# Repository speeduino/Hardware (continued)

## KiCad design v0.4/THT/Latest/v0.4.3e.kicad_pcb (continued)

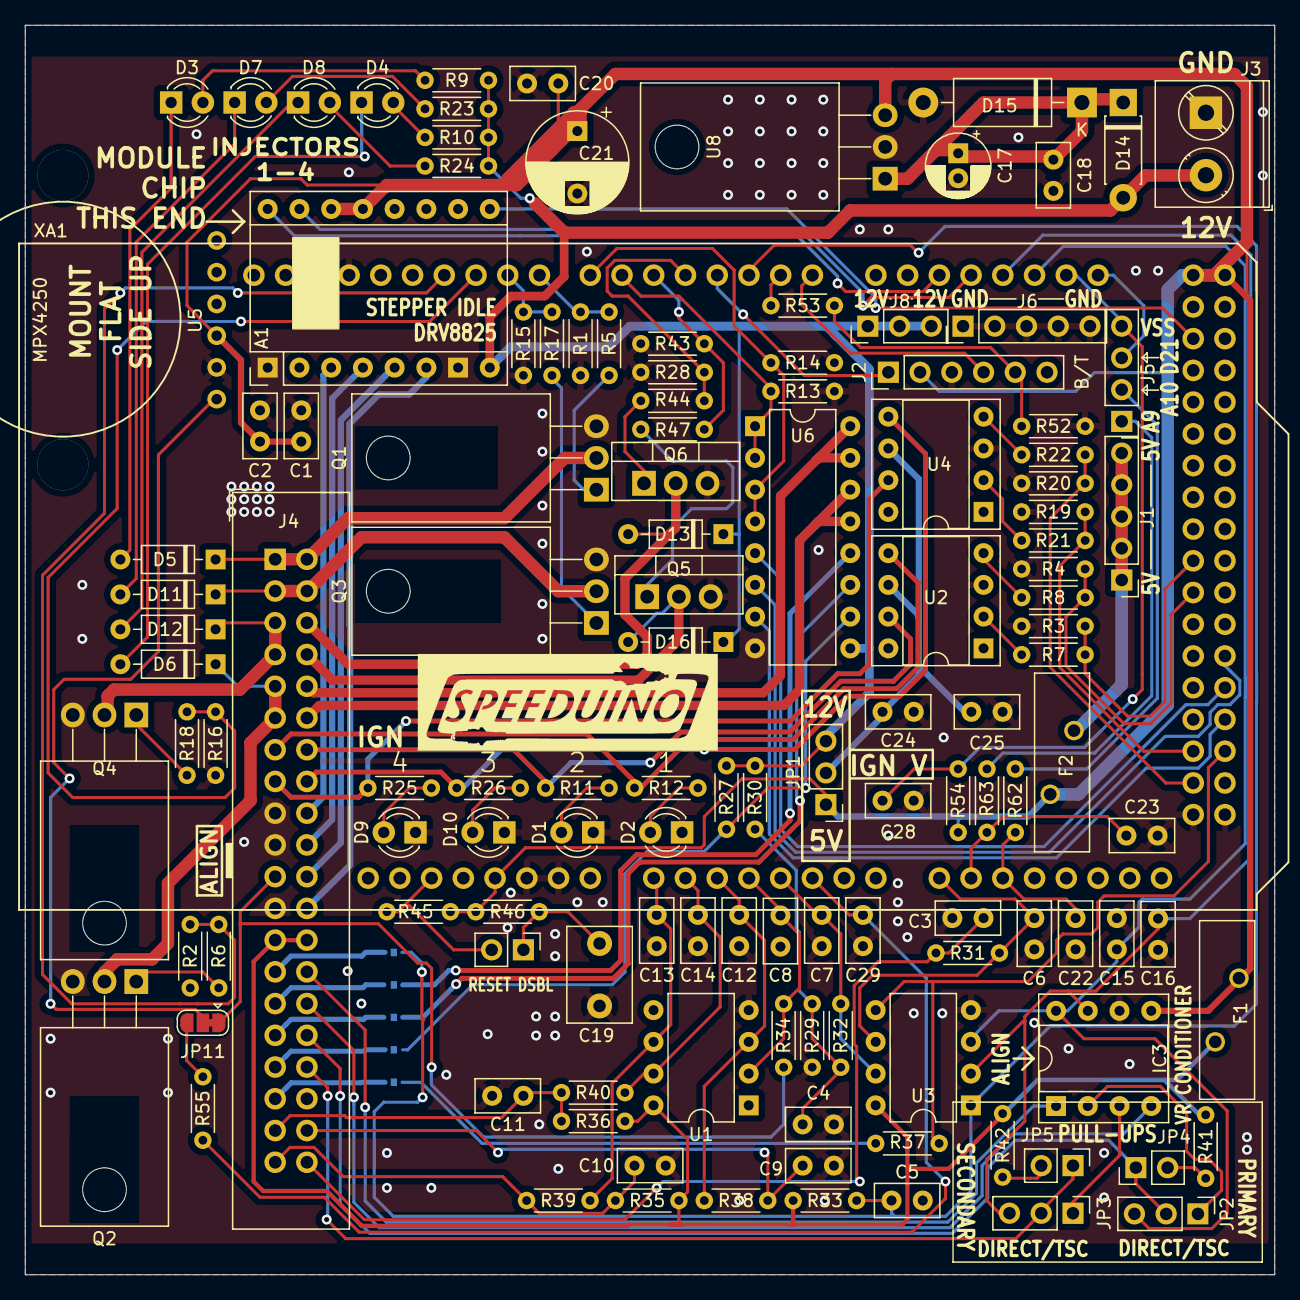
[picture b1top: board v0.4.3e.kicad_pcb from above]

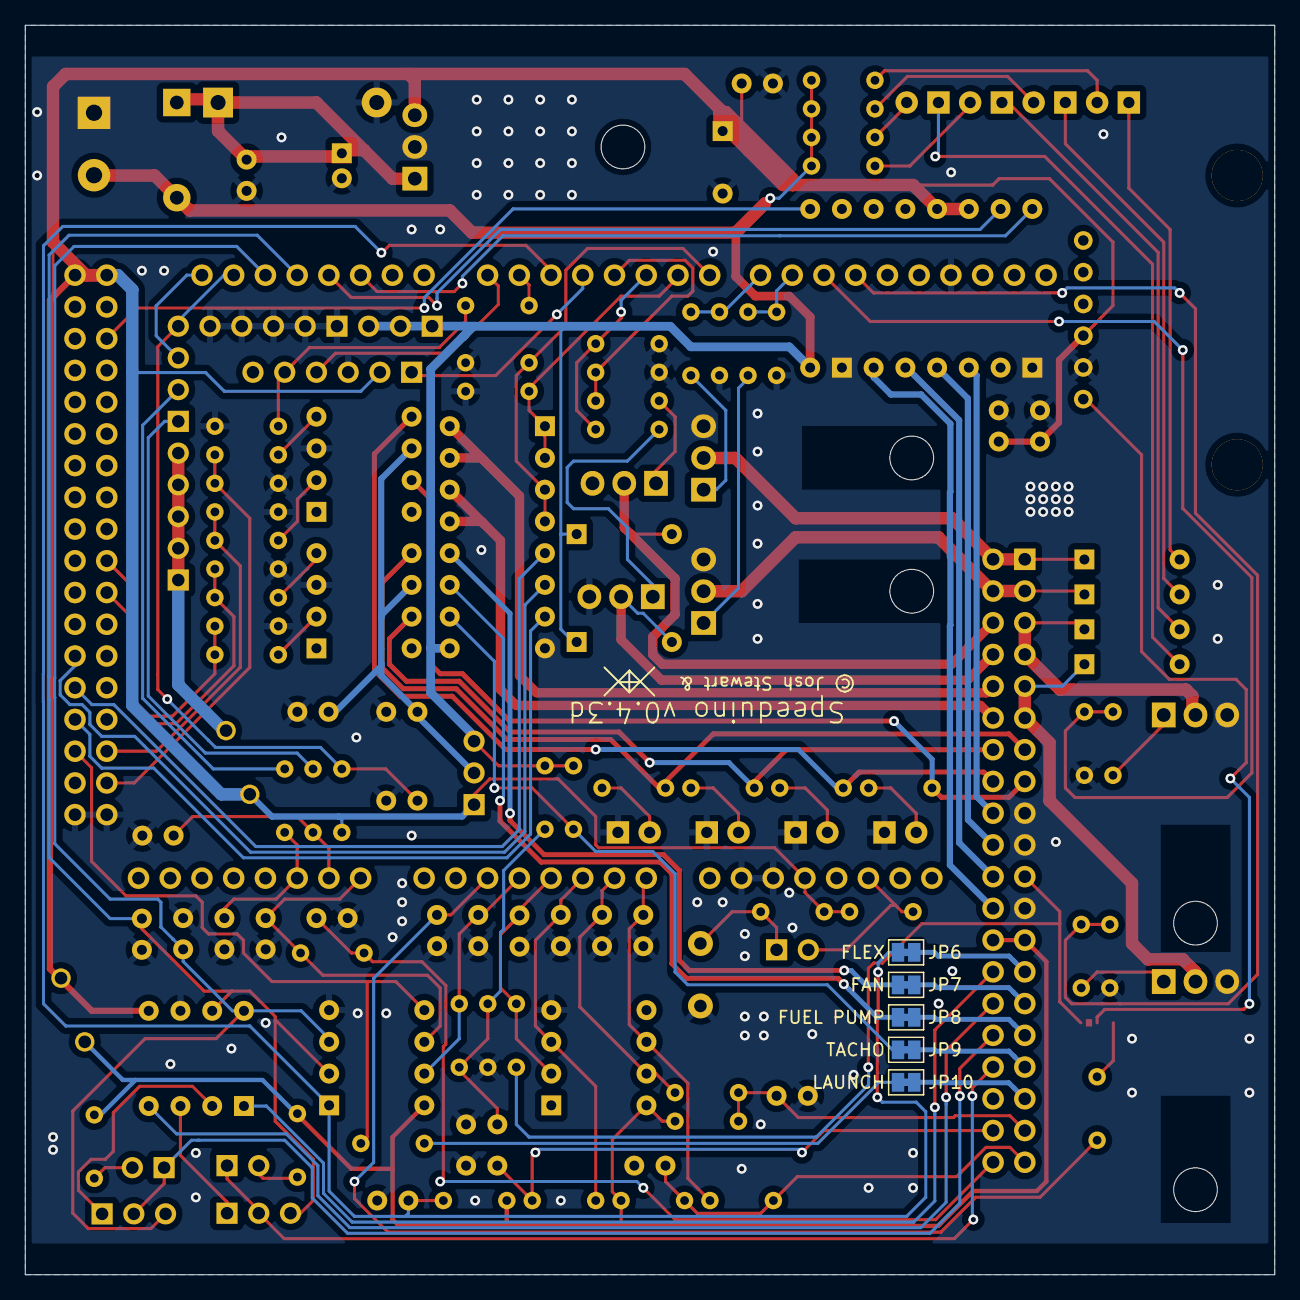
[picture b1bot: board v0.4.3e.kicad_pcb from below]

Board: 2 copper layers, 100.0 x 100.0 mm, 133 parts (5 on the bottom side), 111 nets.

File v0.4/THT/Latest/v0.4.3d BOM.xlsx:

| Speeduino BOM |  |  | v0.4.3d
Reference | Quantity | Value | Manufacturer_Name | Manufacturer_Part_Number | Footprint | URL | Digikey Part Number | Digikey BOM import
A1 | 2 | DRV8825 socket | Sullins | PPTC081LFBN-RC | Module:Pololu_Breakout-16_15.2x20.3mm | https://www.digikey.com.au/products/en?keywords=PPTC081LFBN-RC | S7006-ND | 2,S7006-ND
C1 C15 | 2 | 0.01uF | TDK | FA18X7R1H103KNU06 | Capacitor_THT:C_Disc_D5.0mm_W2.5mm_P2.50mm | https://www.digikey.com.au/product-detail/en/tdk-corporation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 | 445-174244-1-ND | 2,445-174244-1-ND
C17 | 1 | 10uF | Panasonic | EEU-FC1H100L | Capacitor_THT:CP_Radial_D5.0mm_P2.00mm | https://www.digikey.com.au/product-detail/en/panasonic-elect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 | P10316-ND | 1,P10316-ND
C19 | 1 | 22uF | TDK | FA22X7R1E226MRU06 | Capacitor_THT:C_Disc_D7.5mm_W5.0mm_P5.00mm |  | 445-180603-1-ND | 1,445-180603-1-ND
C21 | 1 | 47uF | Panasonic | EEU-FC1H470B | Capacitor_THT:CP_Radial_D8.0mm_P5.00mm |  | P19658CT-ND | 1,P19658CT-ND
C3 C4 C9 C10 C11 C16 C18 C20 C22 C23 C24 C28 | 12 | 0.1uF | TDK | FA18X8R1E104KNU06 | Capacitor_THT:C_Disc_D5.0mm_W2.5mm_P2.50mm | https://www.digikey.com.au/product-detail/en/tdk-corporation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 | 445-180563-1-ND | 12,445-180563-1-ND
C2 C25 | 2 | 1uF | TDK | FA18X7R1E105KRU06 | Capacitor_THT:C_Disc_D5.0mm_W2.5mm_P2.50mm | https://www.digikey.com.au/product-detail/en/tdk-corporation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 | 445-180543-1-ND | 2,445-180543-1-ND
C5 C6 C7 C12 C13 C14 | 6 | 0.22uF | TDK | FA18X8R1E224KRU06 | Capacitor_THT:C_Disc_D5.0mm_W2.5mm_P2.50mm | https://www.digikey.com.au/product-detail/en/tdk-corporation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 | 445-180564-1-ND | 6,445-180564-1-ND
C8 C29 | 2 | 470pf | TDK | FA18NP01H471JNU06 | Capacitor_THT:C_Disc_D5.0mm_W2.5mm_P2.50mm | https://www.digikey.com.au/product-detail/en/tdk-corporation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 | 445-180522-1-ND | 2,445-180522-1-ND
D5 D6 D11 D12 D13 D16 | 6 | Diode - General purpose | Vishay | 1N914TAP | Diode_THT:D_DO-35_SOD27_P7.62mm_Horizontal | https://www.digikey.com.au/product-detail/en/vishay-general-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 | 1N914TAPGICT-ND | 6,1N914TAPGICT-ND
D14 | 1 | SB230TA | SMC | SB230TA | Diode_THT:D_DO-41_SOD81_P7.62mm_Horizontal | https://www.digikey.com.au/product-detail/en/smc-diode-solut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 | 1655-1518-1-ND | 1,1655-1518-1-ND
D15 | 1 | D_TVS | Littelfuse | TP6KE47A | Diode_THT:D_DO-15_P12.70mm_Horizontal |  | F6853CT-ND | 1,F6853CT-ND
D1 D2 D3 D4 D7 D8 D9 D10 | 8 | LED | Wurth | 151031SS04000 | LED_THT:LED_D3.0mm | https://www.digikey.com.au/product-detail/en/w%C3%BCrth-elek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 | 732-5005-ND | 8,732-5005-ND
F1 F2 | 2 | Polyfuse | Bel Fuse | 0ZRP0050FF1E | Fuse:Fuse_BelFuse_0ZRE0055FF_L14.0mm_W4.1mm | https://www.digikey.com.au/product-detail/en/bel-fuse-inc/0Z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 | 507-2403-ND | 2,507-2403-ND
IC3 | 2 | Trig Cond Socket | Sullins Connector Solutions | PPTC041LFBN-RC | Package_DIP:DIP-8_W7.62mm_Socket |  | S7002-ND | 2,S7002-ND
J4 | 1 | Conn_02x20_Counter_Clockwise | Sullins | SBH11-PBPC-D20-ST-BK | Connector_IDC:IDC-Header_2x20_P2.54mm_Vertical | https://www.digikey.com.au/product-detail/en/sullins-connect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 | S9175-ND | 1,S9175-ND
Q1 Q2 Q3 Q4 | 4 | N-Channel MOSFET | ST | STP62NS04Z | Package_TO_SOT_THT:TO-220-3_Horizontal_TabDown |  | 497-5896-5-ND | 4,497-5896-5-ND
Q5 Q6 | 2 | Q_NMOS_GDSD | Vishay | IRLD024PBF | Package_DIP:Vishay_HVM-DIP-3_W7.62mm | https://www.digikey.com.au/product-detail/en/vishay-siliconi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 | IRLD024PBF-ND | 2,IRLD024PBF-ND
R1 R2 R3 R4 R13 R14 R15 R16 R19 R20 R28 R43 | 12 | 100k | Vishay | MBA02040C1003FCT00 | Resistor_THT:R_Axial_DIN0204_L3.6mm_D1.6mm_P5.08mm_Horizontal | https://www.digikey.com.au/product-detail/en/vishay-beyschla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 | BC3240CT-ND | 12,BC3240CT-ND
R9 R10 R11 R12 R23 R24 R25 R26 R33 | 9 | 2.4k | Vishay | MBA02040C2401FC100 | Resistor_THT:R_Axial_DIN0204_L3.6mm_D1.6mm_P5.08mm_Horizontal | https://www.digikey.com.au/product-detail/en/vishay-beyschla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 | BC3483CT-ND | 9,BC3483CT-ND
R30 | 1 | 3.9k | Vishay | MBA02040C3901FCT00 | Resistor_THT:R_Axial_DIN0204_L3.6mm_D1.6mm_P5.08mm_Horizontal | https://www.digikey.com.au/product-detail/en/vishay-beyschla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 | BC3272CT-ND | 1,BC3272CT-ND
R31 R32 R34 R38 R39 R40 R55 R62 R63 | 9 | 470R | Vishay | MBA02040C4700FRP00 | Resistor_THT:R_Axial_DIN0204_L3.6mm_D1.6mm_P5.08mm_Horizontal | https://www.digikey.com.au/product-detail/en/vishay-beyschla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 | BC3516CT-ND | 9,BC3516CT-ND
R35 R36 | 2 | 2.49k | Vishay | MBA02040C2491FRP00 | Resistor_THT:R_Axial_DIN0204_L3.6mm_D1.6mm_P5.08mm_Horizontal | https://www.digikey.com.au/product-detail/en/vishay-beyschla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 | BC2.49KXCT-ND | 2,BC2.49KXCT-ND
R27 R45 | 2 | 10k | Vishay | MBA02040C1002FRP00 | Resistor_THT:R_Axial_DIN0204_L3.6mm_D1.6mm_P5.08mm_Horizontal | https://www.digikey.com.au/product-detail/en/vishay-beyschla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 | BC10.0KXCT-ND | 2,BC10.0KXCT-ND
R46 | 1 | 120R | Vishay | MBA02040C1200FC100 | Resistor_THT:R_Axial_DIN0204_L3.6mm_D1.6mm_P5.08mm_Horizontal |  | BC3453CT-ND | 1,BC3453CT-ND
R5 R6 R7 R8 R17 R18 R21 R22 R29 R37 R41 R42 R44 R47 R53 R54 | 16 | 1k | Vishay | MBA02040C1001FRP00 | Resistor_THT:R_Axial_DIN0204_L3.6mm_D1.6mm_P5.08mm_Horizontal |  | BC1.00KXCT-ND | 16,BC1.00KXCT-ND
R52 | 1 | 2k | Vishay | MBA02040C2001FCT00 | Resistor_THT:R_Axial_DIN0204_L3.6mm_D1.6mm_P5.08mm_Horizontal | https://www.digikey.com.au/product-detail/en/vishay-beyschla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 | BC3254CT-ND | 1,BC3254CT-ND
U1 U3 | 2 | SP721 | Littelfuse | SP721APP | Package_DIP:DIP-8_W7.62mm |  | F2720-ND | 2,F2720-ND
U2 U4 | 2 | TC4424A | Microchip | TC4424AVPA | Package_DIP:DIP-8_W7.62mm_Socket | https://www.digikey.com.au/product-detail/en/microchip-techn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 | TC4424AVPA-ND | 2,TC4424AVPA-ND
U5 | 1 | MPX4250 | NXP | MPX4250AP | Misc:MPX4250 | https://www.digikey.com.au/product-detail/en/nxp-usa-inc/MPX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 | MPX4250AP-ND | 1,MPX4250AP-ND
U6 | 1 | ULN2003 | TI | ULN2003AIN‎ | Package_DIP:DIP-16_W7.62mm | https://www.digikey.com.au/product-detail/en/texas-instrumen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 | 296-16971-5-ND | 1,296-16971-5-ND
U8 | 1 | LM2940S-5.0 | ON Semi | NCV7805BTG | Package_TO_SOT_THT:TO-220-3_Horizontal_TabDown | https://www.digikey.com.au/product-detail/en/on-semiconducto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 | NCV7805BTGOS-ND | 1,NCV7805BTGOS-ND

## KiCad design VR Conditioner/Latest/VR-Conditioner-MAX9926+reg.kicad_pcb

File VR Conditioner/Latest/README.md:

### 2023-01-22
Most significant change is to correct the Channel 1 polarity of previous version.
In practise everyone seems to try their VR pick-up in both polarities before settling on the best for their set-up.
Tidied the silkscreen a lot to improve readability. Removed component IDs from silkscreen. Still on the FAB layer.
Moved a regulator & edge pin header slightly to make soldering easier.
Re-routed traces from header pins 1 & 2 so that either could be cut if you wanted to mix VR & a piggy-backed opto-isolator.
Also update because KiCAD v6.x seems to have moved a lot of things.

### 2022-09-10
Received a batch of v3.73 boards & bench-tested using 13 year-old Crankshaft Position Sensor 7674201-01 from 2009 BMW F800R 
and a metal 'L' hook screw in a hand drill at about 1000 rpm. All OK on 5V & also on 12V with a TS78L05CT TO-92 regulator.

### 2022-08-14
Replace linear regulator with more robust choice. Move U1 & C4 to make space. Adjust all tracks as required including widening. 
Updated BOM.  I will shortly be ordering a run of these, e-mail if you're interested: TechColab.co.je [at] Gmail.con

### 2022-08-07
Added test-pads which can be used to solder directly when not using socket mount, E.g. when placing the VR conditioner as close as possible to the engine sensors in noisy environments. Improved ground plane shielding & much improved silk screen labelling. Tried to fit an official OpenSource Hardware logo but even the smallest is too big. Update to KiCAD v6.x so 3D renders now without components.  N.B. To be clear, this board is for VR only & does not support an opto-isolator option.

### 2021-02-23
I have not made & tested this design but it is barely changed from the manufacrurers data sheets or other designs.
If you make & test it then please advise.

I'm new to KiCAD so I don't know how to do some things.  Such as how to have an 8-pin set of holes without a 3D chip sitting in it.
Or how to do an 8-pin header in the shape & pin count order of a chip.

### 2021-02-24
Changed version number to 3.5 so that it reflects relative cronology from previous design.
Renamed this from Notes.txt to README.md & corrected the date above.
Added Comments to schematic, inc. single-sided design allowing 'Letter' postage!
Updated BOM in schematic to reflect readily available parts found on OctoPart.

### 2021-04-22
Goal: give the left 6 passive components some space from the edge.
Increase size/power of some SMT resistors where suggested.
Re-route COUT1 from DIP.8 to SIL.4 in green so no signal traces are by the edge.
Shift right 5 components slightly right.
Shift DIP, chip & hidden cap slightly right.
Shift left 6 components slightly right.
Re-route left 6 components to avoid side swapping.
Ensure GND plane encircles everything with a via in each corner.
Tidy with some symetry.
Ensure all 'thin' traces are 0.20mm (up from 0.16)

### 2021-08-16
Move to it's own project to reflect that Speeduino main project has dropped all VRs.
Re-applied logical resistor numbering.  Bumped schematic v to 3.7 to match PCB.

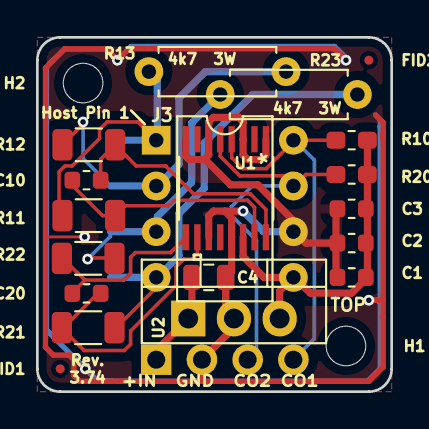
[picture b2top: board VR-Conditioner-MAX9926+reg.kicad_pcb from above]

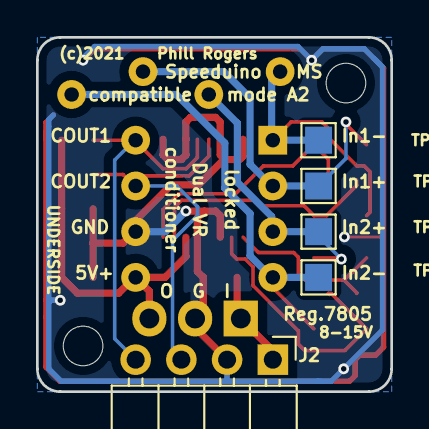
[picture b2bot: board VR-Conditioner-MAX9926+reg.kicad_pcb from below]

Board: 2 copper layers, 19.7 x 19.7 mm, 26 parts (5 on the bottom side), 13 nets.

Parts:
C1: 10n; C_0603_1608Metric
C2: 100n; C_0603_1608Metric
C3: 1u; C_0603_1608Metric
C4: 10u; C_0805_2012Metric
C10, C20: 1n; C_0603_1608Metric
FID1, FID2: Fiducial; Fiducial_0.5mm_Mask1mm
H1, H2: MountingHole; MountingHole_2.2mm_M2
J2: Edge; PinHeader_1x04_P2.54mm_Horizontal
J3: 8-pin header; DIP-8_W7.62mm
R10, R20: 1k; R_0603_1608Metric_Pad1.05x0.95mm_HandSolder
R11, R12, R21, R22: 10k; R_1206_3216Metric
R13, R23: 4.7k; R_Axial_DIN0207_L6.3mm_D2.5mm_P7.62mm_Horizontal
TP1, TP2, TP3, TP4: TP; TestPoint_Pad_1.5x1.5mm
U1: locked; MAX9926UAEE&plus_
U2: L7805; TO-220-3_Vertical

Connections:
+12V: C4.1, J2.1, U2.1 (IN)
/COUT1: J2.4, J3.8, R10.2, U1.4 (COUT1)
/COUT2: J2.3, J3.7, R20.2, U1.5 (COUT2)
GND: C1.2, C2.2, C3.2, C4.2, J2.2, J3.6, U1.1 (INT_THRS1), U1.3 (BIAS1), U1.6 (BIAS2), U1.8 (INT_THRS2), U1.11 (GND), U1.13 (ZERO_EN), U2.2 (GND)
unnamed: C10.1, R12.1, U1.16 (IN1+)
unnamed: C10.2, R11.1, U1.15 (IN1-)
unnamed: C20.1, R21.2, U1.10 (IN2-)
unnamed: C20.2, R22.2, U1.9 (IN2+)
unnamed: J3.1, R11.2, R13.1, TP1.1
unnamed: J3.2, R12.2, R13.2, TP2.1
unnamed: J3.3, R22.1, R23.1, TP3.1
unnamed: J3.4, R21.1, R23.2, TP4.1
VCC: C1.1, C2.1, C3.1, J3.5, R10.1, R20.1, U1.14 (VCC), U2.3 (OUT)

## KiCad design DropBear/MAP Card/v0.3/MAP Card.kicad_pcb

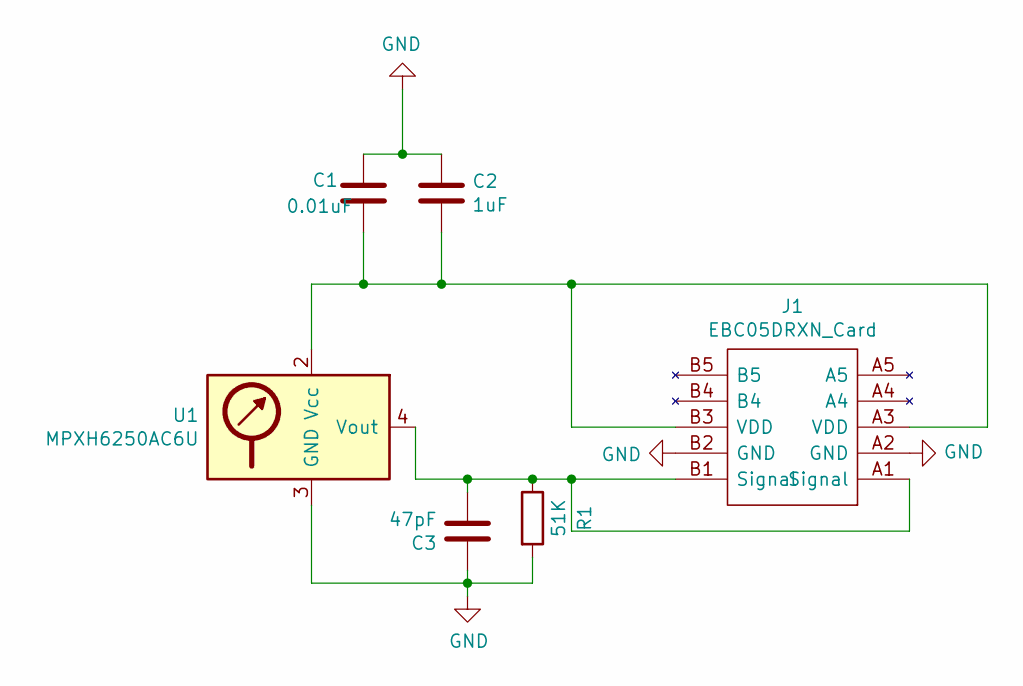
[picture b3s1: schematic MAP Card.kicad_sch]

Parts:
C1: 0.01uF; C_0805_2012Metric; Manufacturer_Part_Number CC0805KRX7R9BB103; Digikey Part Number 311-1136-1-ND
C2: 1uF; C_0805_2012Metric; Manufacturer_Part_Number CC0805KKX7R7BB105; Digikey Part Number 311-1365-1-ND
C3: 47pF; C_0805_2012Metric; Manufacturer_Part_Number C0805C470J5GACAUTO; Digikey Part Number 399-6963-1-ND
J1: EBC05DRXN_Card; Sullins_EBC05DRXN_2x05_P2.54mm_Edge; Manufacturer_Part_Number EBC05DRXN
R1: 51K; R_0805_2012Metric; Manufacturer_Part_Number RC0805FR-0751KL; Digikey Part Number 311-51.0KCRCT-ND
U1: MPXH6250AC6U; Manufacturer_Part_Number MPXH6250AC6U; Digikey Part Number MPXH6250AC6U-ND

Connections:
GND: C1.1, C2.1, C3.1, J1.A2 (GND), J1.B2 (GND), R1.2, U1.3 (GND)
unnamed: C1.2, C2.2, J1.A3 (VDD), J1.B3 (VDD), U1.2 (Vcc)
unnamed: C3.2, J1.A1 (Signal), J1.B1 (Signal), R1.1, U1.4 (Vout)

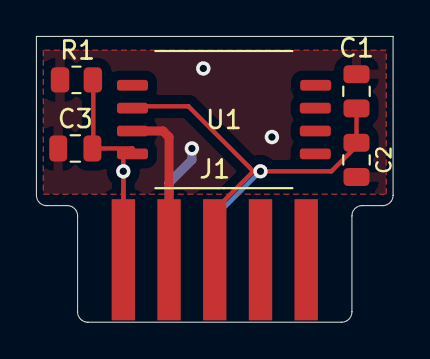
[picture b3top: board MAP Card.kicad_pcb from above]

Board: 2 copper layers, 19.8 x 15.9 mm, 6 parts (0 on the bottom side), 3 nets.

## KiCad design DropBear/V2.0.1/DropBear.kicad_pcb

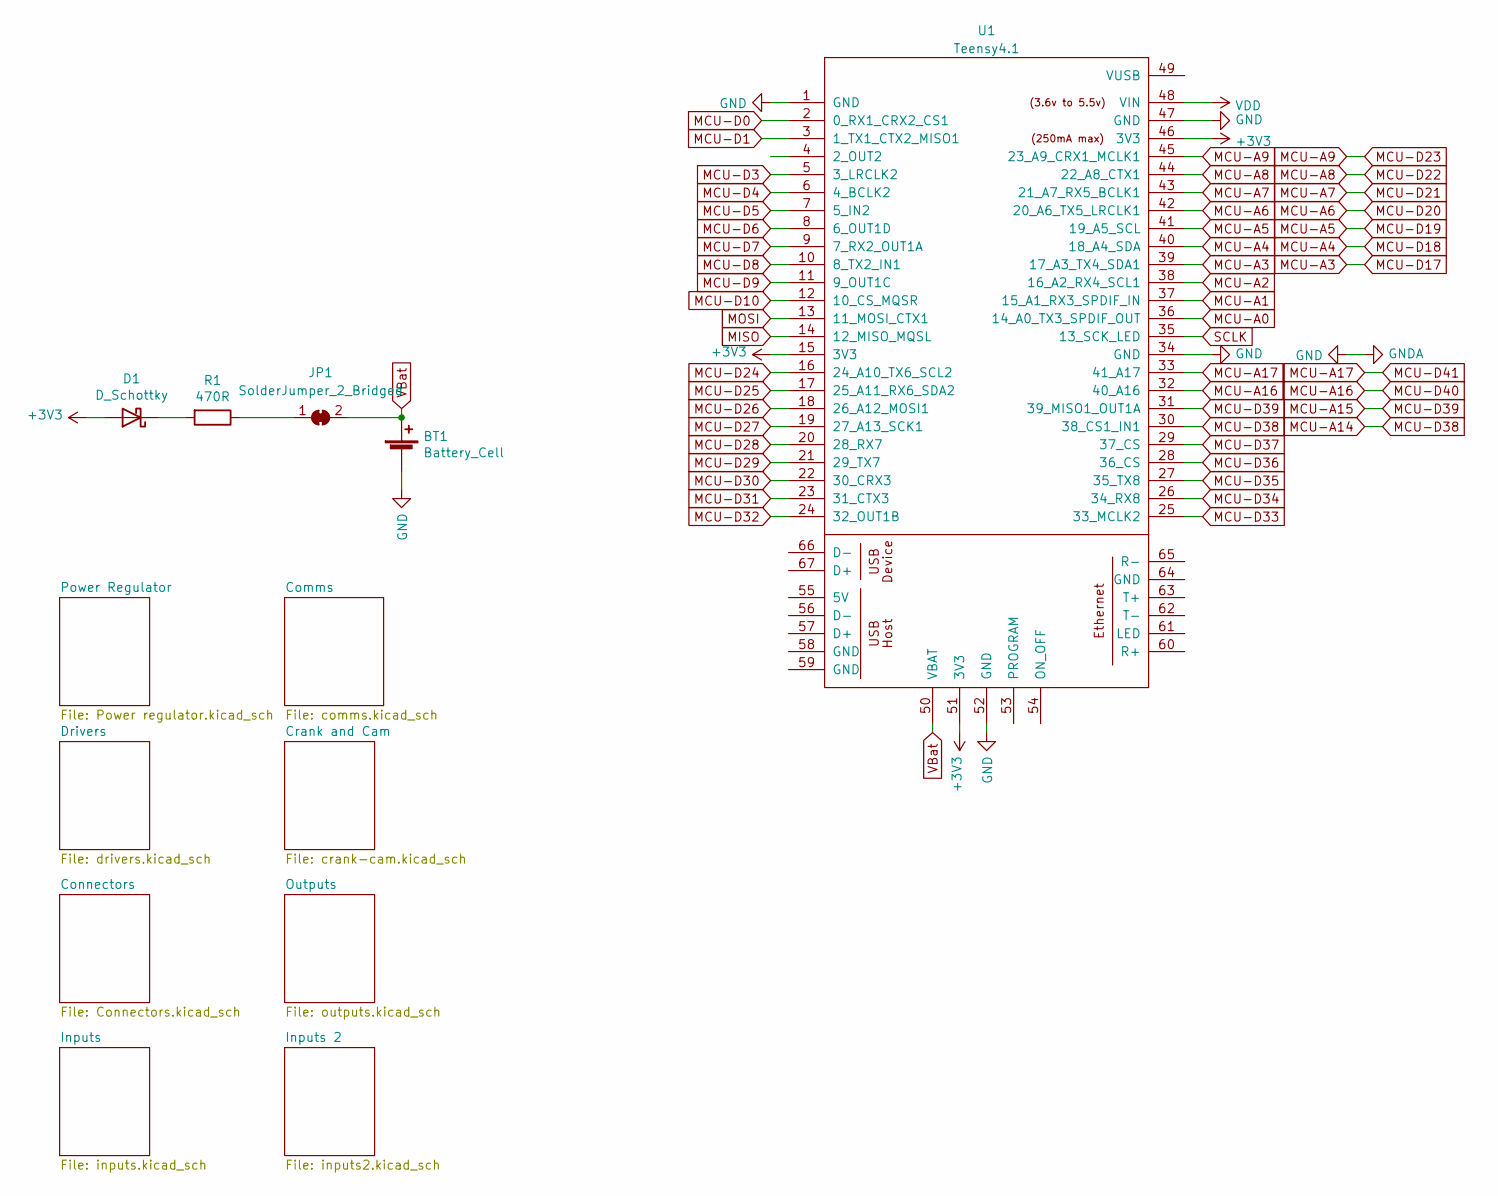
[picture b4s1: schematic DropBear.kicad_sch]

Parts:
BT1: Battery_Cell; BatteryHolder_Keystone_500; Manufacturer_Part_Number 500; Digikey Part Number 36-500-ND
D1: D_Schottky; D_PowerDI-123; Manufacturer_Part_Number DFLS2100-7; Digikey Part Number DFLS2100-7DICT-ND
JP1: SolderJumper_2_Bridged; SolderJumper-2_P1.3mm_Bridged_Pad1.0x1.5mm
R1: 470R; R_0805_2012Metric; Manufacturer_Part_Number ERJ-6ENF4700V; Digikey Part Number P470CCT-ND
U1: Teensy4.1; Teensy41

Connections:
+3V3: D1.2 (A), U1.15 (3V3), U1.46 (3V3), U1.51 (3V3); also elsewhere on the board
+5V: U1.48 (VIN); also elsewhere on the board
ADC-Clamp-1: U1.36 (14_A0_TX3_SPDIF_OUT); also elsewhere on the board
ADC-Clamp-4: U1.32 (40_A16); also elsewhere on the board
ADC-Clamp-5: U1.29 (37_CS); also elsewhere on the board
ADC-Clamp-6: U1.28 (36_CS); also elsewhere on the board
ADC-Clamp-7: U1.31 (39_MISO1_OUT1A); also elsewhere on the board
ADC-Clamp-10: U1.33 (41_A17); also elsewhere on the board
ADC-Clamp-12: U1.37 (15_A1_RX3_SPDIF_IN); also elsewhere on the board
ADC-Clamp-13: U1.38 (16_A2_RX4_SCL1); also elsewhere on the board
ADC-Clamp-14: U1.39 (17_A3_TX4_SDA1); also elsewhere on the board
GND: BT1.2 (-), U1.1 (GND), U1.34 (GND), U1.47 (GND), U1.52 (GND); also elsewhere on the board
MC33810_1-CS: U1.12 (10_CS_MQSR); also elsewhere on the board
MC33810_2-CS: U1.11 (9_OUT1C); also elsewhere on the board
MCU-A4: U1.40 (18_A4_SDA); also elsewhere on the board
MCU-A5: U1.41 (19_A5_SCL); also elsewhere on the board
MCU-A6: U1.42 (20_A6_TX5_LRCLK1); also elsewhere on the board
MCU-A7: U1.43 (21_A7_RX5_BCLK1); also elsewhere on the board
MCU-A8: U1.44 (22_A8_CTX1); also elsewhere on the board
MCU-A9: U1.45 (23_A9_CRX1_MCLK1); also elsewhere on the board
MCU-A14: U1.30 (38_CS1_IN1)
MCU-D0: U1.2 (0_RX1_CRX2_CS1); also elsewhere on the board
MCU-D1: U1.3 (1_TX1_CTX2_MISO1)
MCU-D3: U1.5 (3_LRCLK2)
MCU-D4: U1.6 (4_BCLK2)
MCU-D5: U1.7 (5_IN2); also elsewhere on the board
MCU-D6: U1.8 (6_OUT1D); also elsewhere on the board
MCU-D7: U1.9 (7_RX2_OUT1A); also elsewhere on the board
MCU-D8: U1.10 (8_TX2_IN1); also elsewhere on the board
MCU-D24: U1.16 (24_A10_TX6_SCL2); also elsewhere on the board
MCU-D25: U1.17 (25_A11_RX6_SDA2); also elsewhere on the board
MCU-D26: U1.18 (26_A12_MOSI1); also elsewhere on the board
MCU-D27: U1.19 (27_A13_SCK1); also elsewhere on the board
MCU-D28: U1.20 (28_RX7); also elsewhere on the board
MCU-D29: U1.21 (29_TX7); also elsewhere on the board
MCU-D30: U1.22 (30_CRX3); also elsewhere on the board
MCU-D31: U1.23 (31_CTX3); also elsewhere on the board
MCU-D32: U1.24 (32_OUT1B); also elsewhere on the board
MCU-D33: U1.25 (33_MCLK2)
MCU-D34: U1.26 (34_RX8); also elsewhere on the board
MCU-D35: U1.27 (35_TX8); also elsewhere on the board
MISO: U1.14 (12_MISO_MQSL); also elsewhere on the board
MOSI: U1.13 (11_MOSI_CTX1); also elsewhere on the board
unnamed: D1.1 (K), R1.2
unnamed: JP1.1 (A), R1.1
SCLK: U1.35 (13_SCK_LED); also elsewhere on the board
VBat: BT1.1 (+), JP1.2 (B), U1.50 (VBAT)

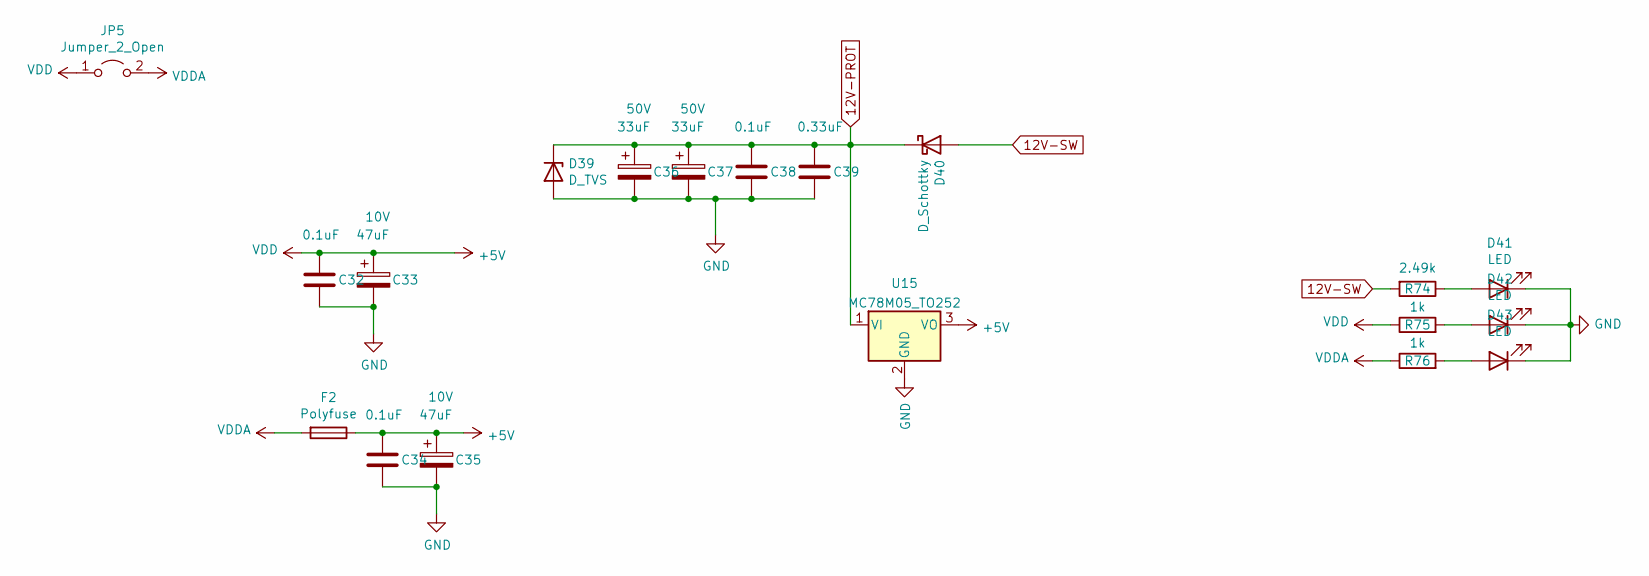
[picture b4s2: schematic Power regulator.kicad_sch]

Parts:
C32, C34, C38: 0.1uF; C_0805_2012Metric; Manufacturer_Part_Number CC0805KRX7R9BB104; Digikey Part Number 311-1140-1-ND
C33, C35: 47uF; CP_EIA-3528-21_Kemet-B; Voltage 10V; Manufacturer_Part_Number TAJB476K006RNJ; Digikey Part Number 478-1692-1-ND
C36, C37: 33uF; CP_Elec_6.3x7.7; Voltage 50V; Manufacturer_Part_Number EEE-1HA330XP; Digikey Part Number PCE3925CT-ND
C39: 0.33uF; C_0805_2012Metric; Manufacturer_Part_Number CGA4J2X7R1H334K125AA; Digikey Part Number 445-5684-1-ND
D39: D_TVS; D_SMB; Manufacturer_Part_Number SMBJ40A-Q; Digikey Part Number SMBJ40A-QCT-ND
D40: D_Schottky; D_SMA_Handsoldering; Manufacturer_Part_Number B360A-13-F; Digikey Part Number B360A-FDICT-ND
D41, D42, D43: LED; LED_0805_2012Metric; Manufacturer_Part_Number LG R971-KN-1; Digikey Part Number 475-1410-2-ND
F2: Polyfuse; Fuse_0603_1608Metric; Manufacturer_Part_Number 0ZCM0008FF2G; Digikey Part Number 507-1817-1-ND
JP5: Jumper_2_Open; SolderJumper-2_P1.3mm_Open_Pad1.0x1.5mm
R74: 2.49k; R_0805_2012Metric; Tolerance 0.1%; Manufacturer_Part_Number RT0805BRD072K49L; Digikey Part Number YAG1854CT-ND
R75, R76: 1k; R_0805_2012Metric; Manufacturer_Part_Number RC0805FR-071KL; Digikey Part Number 311-1.00KCRCT-ND
U15: MC78M05_TO252; TO-252-2; Manufacturer_Part_Number NCV7805BDTRKG; Digikey Part Number NCV7805BDTRKGOSCT-ND

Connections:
12V-PROT: C36.1, C37.1, C38.1, C39.1, D39.1 (K), D40.1 (K), U15.1 (VI)
12V-SW: D40.2 (A), R74.2; also elsewhere on the board
+5V: C32.1, C33.1, C34.1, C35.1, F2.1, JP5.1 (A), R75.1, U15.3 (VO); also elsewhere on the board
GND: C32.2, C33.2, C34.2, C35.2, C36.2, C37.2, C38.2, C39.2, D39.2 (A), D41.1 (K), D42.1 (K), D43.1 (K), U15.2 (GND); also elsewhere on the board
unnamed: D41.2 (A), R74.1
unnamed: D42.2 (A), R75.2
unnamed: D43.2 (A), R76.2
VDDA: F2.2, JP5.2 (B), R76.1; also elsewhere on the board

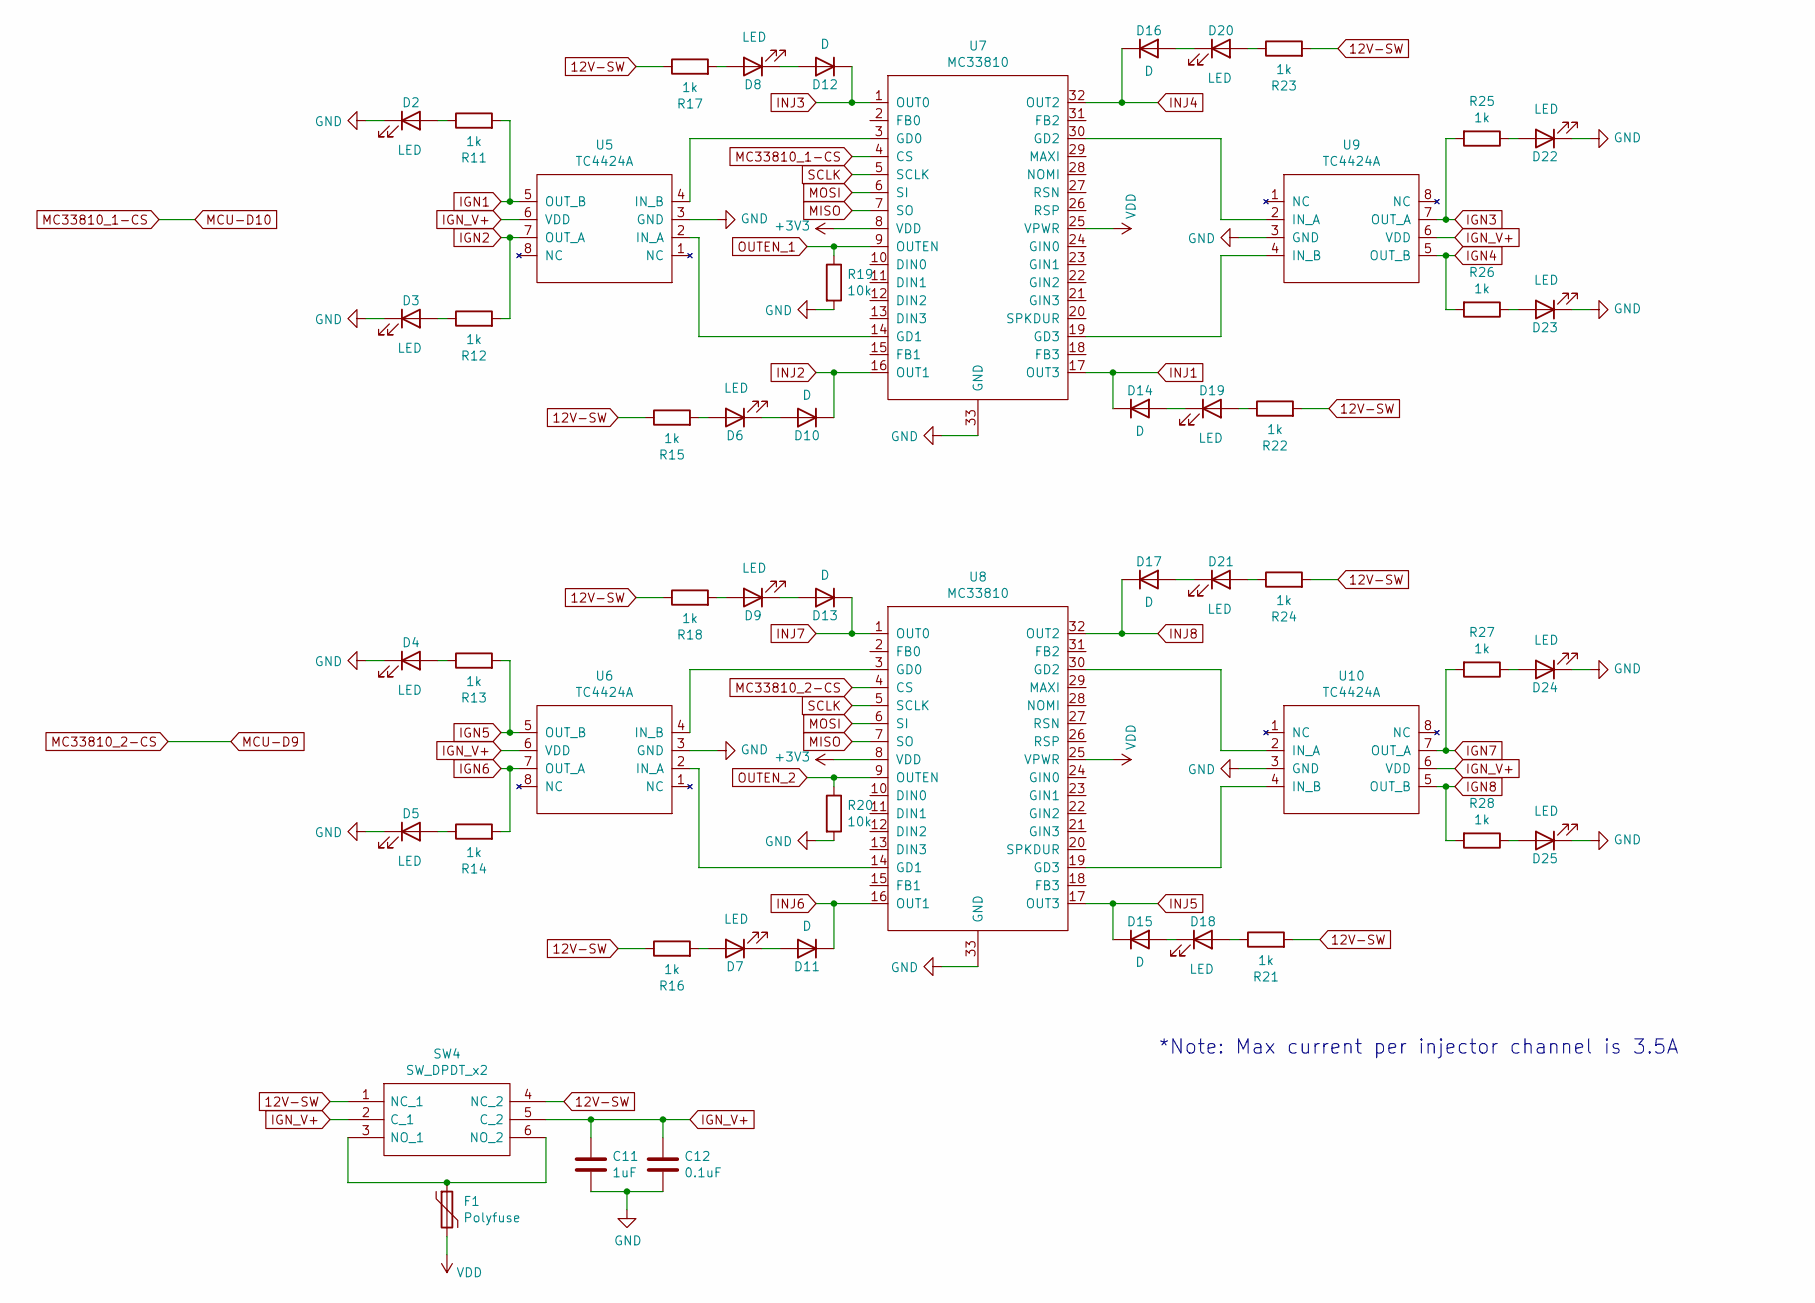
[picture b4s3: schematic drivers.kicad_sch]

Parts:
C11: 1uF; C_0805_2012Metric; Manufacturer_Part_Number CC0805KKX7R7BB105; Digikey Part Number 311-1365-1-ND
C12: 0.1uF; C_0805_2012Metric; Manufacturer_Part_Number CC0805KRX7R9BB104; Digikey Part Number 311-1140-1-ND
D2, D3, D4, D5, D22, D23, D24, D25: LED; LED_0805_2012Metric; Manufacturer_Part_Number SML-H12D8TT86C; Digikey Part Number SML-H12D8TT86CCT-ND
D6, D7, D8, D9, D18, D19, D20, D21: LED; LED_0805_2012Metric; Manufacturer_Part_Number LH R974-LP-1; Digikey Part Number 475-1415-1-ND
D10, D11, D12, D13, D14, D15, D16, D17: D; D_SOD-323; Manufacturer_Part_Number 1N4448WX-TP; Digikey Part Number 1N4448WXTPMSCT-ND
F1: Polyfuse; Fuse_1812_4532Metric; Manufacturer_Part_Number 0ZCC0050FF2C; Digikey Part Number 507-1361-1-ND
R11, R12, R13, R14, R15, R16, R17, R18, R21, R22, R23, R24, R25, R26, R27, R28: 1k; R_0805_2012Metric; Manufacturer_Part_Number RC0805FR-071KL; Digikey Part Number 311-1.00KCRCT-ND
R19, R20: 10k; R_0805_2012Metric; Manufacturer_Part_Number RC0805JR-0710KL; Digikey Part Number 311-10KARCT-ND
SW4: SW_DPDT_x2; AYZ0202AGRLC; Manufacturer_Part_Number AYZ0202AGRLC; Digikey Part Number 401-2013-1-ND
U5, U6, U9, U10: TC4424A; SOIC-8_3.9x4.9mm_P1.27mm; Manufacturer_Part_Number TC4424AVOA; Digikey Part Number TC4424AVOA-ND
U7, U8: MC33810; SOIC32-P0.65-33N; Manufacturer_Part_Number MCZ33810EK

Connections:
12V-SW: R15.1, R16.1, R17.1, R18.1, R21.2, R22.2, R23.2, R24.2, SW4.1 (NC_1), SW4.4 (NC_2); also elsewhere on the board
+3V3: U7.8 (VDD), U8.8 (VDD); also elsewhere on the board
+5V: F1.2, U7.25 (VPWR), U8.25 (VPWR); also elsewhere on the board
GND: C11.2, C12.2, D2.1 (K), D3.1 (K), D4.1 (K), D5.1 (K), D22.1 (K), D23.1 (K), D24.1 (K), D25.1 (K), R19.2, R20.2, U5.3 (GND), U6.3 (GND), U7.33 (GND), U8.33 (GND), U9.3 (GND), U10.3 (GND); also elsewhere on the board
IGN1: R11.2, U5.5 (OUT_B); also elsewhere on the board
IGN2: R12.2, U5.7 (OUT_A); also elsewhere on the board
IGN3: R25.2, U9.7 (OUT_A); also elsewhere on the board
IGN4: R26.2, U9.5 (OUT_B); also elsewhere on the board
IGN5: R13.2, U6.5 (OUT_B); also elsewhere on the board
IGN6: R14.2, U6.7 (OUT_A); also elsewhere on the board
IGN7: R27.2, U10.7 (OUT_A); also elsewhere on the board
IGN8: R28.2, U10.5 (OUT_B); also elsewhere on the board
IGN_V+: C11.1, C12.1, SW4.2 (C_1), SW4.5 (C_2), U5.6 (VDD), U6.6 (VDD), U9.6 (VDD), U10.6 (VDD)
INJ1: D14.1 (K), U7.17 (OUT3); also elsewhere on the board
INJ2: D10.1 (K), U7.16 (OUT1); also elsewhere on the board
INJ3: D12.1 (K), U7.1 (OUT0); also elsewhere on the board
INJ4: D16.1 (K), U7.32 (OUT2); also elsewhere on the board
INJ5: D15.1 (K), U8.17 (OUT3); also elsewhere on the board
INJ6: D11.1 (K), U8.16 (OUT1); also elsewhere on the board
INJ7: D13.1 (K), U8.1 (OUT0); also elsewhere on the board
INJ8: D17.1 (K), U8.32 (OUT2); also elsewhere on the board
MC33810_1-CS: U7.4 (CS); also elsewhere on the board
MC33810_2-CS: U8.4 (CS); also elsewhere on the board
MISO: U7.7 (SO), U8.7 (SO); also elsewhere on the board
MOSI: U7.6 (SI), U8.6 (SI); also elsewhere on the board
unnamed: D2.2 (A), R11.1
unnamed: D3.2 (A), R12.1
unnamed: D4.2 (A), R13.1
unnamed: D5.2 (A), R14.1
unnamed: D6.2 (A), R15.2
unnamed: D7.2 (A), R16.2
unnamed: D8.2 (A), R17.2
unnamed: D9.2 (A), R18.2
unnamed: D6.1 (K), D10.2 (A)
unnamed: D7.1 (K), D11.2 (A)
unnamed: D8.1 (K), D12.2 (A)
unnamed: D9.1 (K), D13.2 (A)
unnamed: D14.2 (A), D19.1 (K)
unnamed: D15.2 (A), D18.1 (K)
unnamed: D16.2 (A), D20.1 (K)
unnamed: D17.2 (A), D21.1 (K)
unnamed: D18.2 (A), R21.1
unnamed: D19.2 (A), R22.1
unnamed: D20.2 (A), R23.1
unnamed: D21.2 (A), R24.1
unnamed: D22.2 (A), R25.1
unnamed: D23.2 (A), R26.1
unnamed: D24.2 (A), R27.1
unnamed: D25.2 (A), R28.1
unnamed: F1.1, SW4.3 (NO_1), SW4.6 (NO_2)
unnamed: U5.2 (IN_A), U7.14 (GD1)
unnamed: U5.4 (IN_B), U7.3 (GD0)
unnamed: U6.2 (IN_A), U8.14 (GD1)
unnamed: U6.4 (IN_B), U8.3 (GD0)
unnamed: U7.30 (GD2), U9.2 (IN_A)
unnamed: U7.19 (GD3), U9.4 (IN_B)
unnamed: U8.30 (GD2), U10.2 (IN_A)
unnamed: U8.19 (GD3), U10.4 (IN_B)
OUTEN_1: R19.1, U7.9 (OUTEN)
OUTEN_2: R20.1, U8.9 (OUTEN)
SCLK: U7.5 (SCLK), U8.5 (SCLK); also elsewhere on the board

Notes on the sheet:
*Note: Max current per injector channel is 3.5A

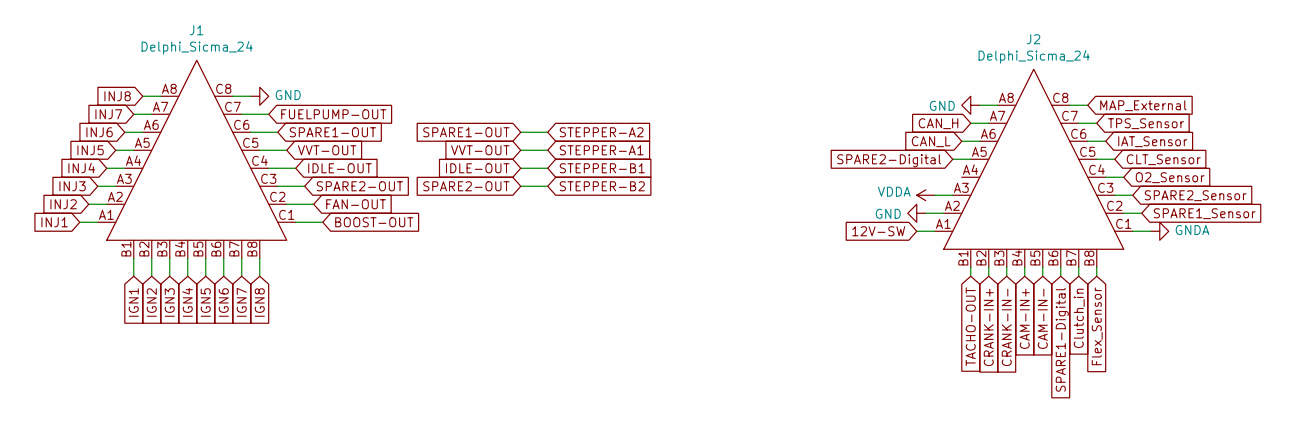
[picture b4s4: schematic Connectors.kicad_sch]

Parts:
J1: Delphi_Sicma_24; Delphi_Sicma_24_Grey
J2: Delphi_Sicma_24; Delphi_Sicma_24_Black

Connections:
12V-SW: J2.A1; also elsewhere on the board
ADC-Clamp-5: J2.B8; also elsewhere on the board
ADC-Clamp-6: J2.B7; also elsewhere on the board
BOOST-OUT: J1.C1; also elsewhere on the board
CAM-IN+: J2.B4; also elsewhere on the board
CAM-IN-: J2.B5; also elsewhere on the board
CAN_H: J2.A7; also elsewhere on the board
CAN_L: J2.A6; also elsewhere on the board
CLT_Sensor: J2.C5; also elsewhere on the board
CRANK-IN+: J2.B2; also elsewhere on the board
CRANK-IN-: J2.B3; also elsewhere on the board
FAN-OUT: J1.C2; also elsewhere on the board
FUELPUMP-OUT: J1.C7; also elsewhere on the board
GND: J1.C8, J2.A2, J2.A8, J2.C1; also elsewhere on the board
IAT_Sensor: J2.C6; also elsewhere on the board
IDLE-OUT: J1.C4; also elsewhere on the board
IGN1: J1.B1; also elsewhere on the board
IGN2: J1.B2; also elsewhere on the board
IGN3: J1.B3; also elsewhere on the board
IGN4: J1.B4; also elsewhere on the board
IGN5: J1.B5; also elsewhere on the board
IGN6: J1.B6; also elsewhere on the board
IGN7: J1.B7; also elsewhere on the board
IGN8: J1.B8; also elsewhere on the board
INJ1: J1.A1; also elsewhere on the board
INJ2: J1.A2; also elsewhere on the board
INJ3: J1.A3; also elsewhere on the board
INJ4: J1.A4; also elsewhere on the board
INJ5: J1.A5; also elsewhere on the board
INJ6: J1.A6; also elsewhere on the board
INJ7: J1.A7; also elsewhere on the board
INJ8: J1.A8; also elsewhere on the board
MAP_External: J2.C8; also elsewhere on the board
O2_Sensor: J2.C4; also elsewhere on the board
SPARE1-Digital: J2.B6; also elsewhere on the board
SPARE1-OUT: J1.C6; also elsewhere on the board
SPARE1_Sensor: J2.C2; also elsewhere on the board
SPARE2-Digital: J2.A5; also elsewhere on the board
SPARE2-OUT: J1.C3; also elsewhere on the board
SPARE2_Sensor: J2.C3; also elsewhere on the board
STEPPER-A1: J1.C5; also elsewhere on the board
TACHO-OUT: J2.B1; also elsewhere on the board
TPS_Sensor: J2.C7; also elsewhere on the board
VDDA: J2.A3; also elsewhere on the board
